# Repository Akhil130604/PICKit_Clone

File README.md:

# PICKit Clone #
📖 About The Project

This project aims to build a fully open-source, cost-effective clone of the Microchip PICKit programmer/debugger. While the original PICKit is a standard tool for PIC microcontrollers, this project seeks to provide a transparent hardware design and firmware implementation that can be studied, modified, and built by the community.

The goal is not just to replicate functionality, but to create a learning platform for embedded programmers and hardware designers interested in:

ICSP (In-Circuit Serial Programming) protocols.

USB Device implementations.

High-voltage generation circuits (VPP).

Low cost hardware.

## ⚠️ Current Status ##

Current Phase: 🚧 Hardware Design & Schematic Capture

We are currently in the initial design phase. The focus is on selecting components, finalizing the power architecture, and routing the initial PCB.

[ ] System Architecture Definition

[ ] Schematic Capture

[ ] PCB Layout

[ ] Prototype Assembly

[ ] Firmware Development

[ ] Testing & Validation

🛠️ Tech Stack & Tools

To view or edit the files, you will need:

EDA Tool: KiCad

Firmware IDE: MPLAB X IDE

## 📂 Repository Structure ##

The repository is currently messed up with unnecesssary files. you are welcome to rearrange it.

Note on Branches:

main: Contains stable, verified releases.

designing: The active design branch. All hardware work happens here.

firmware: The design and development of firmware happens here.

## 🚀 Getting Started ##

Clone the repository:

git clone [https://github.com/Akhil130604/PICKit_Clone.git](https://github.com/Akhil130604/PICKit_Clone.git)

Checkout the branch:

cd PICKit_Clone

git checkout branch

## 🤝 How to Contribute ##

We welcome contributions from the community! Whether it's a code fix, a better PCB routing suggestion, or documentation improvements.

Please read CONTRIBUTING.md for details on our code of conduct and the process for submitting pull requests.

## 📄 License ##

Distributed under the MIT License. See LICENSE for more information.

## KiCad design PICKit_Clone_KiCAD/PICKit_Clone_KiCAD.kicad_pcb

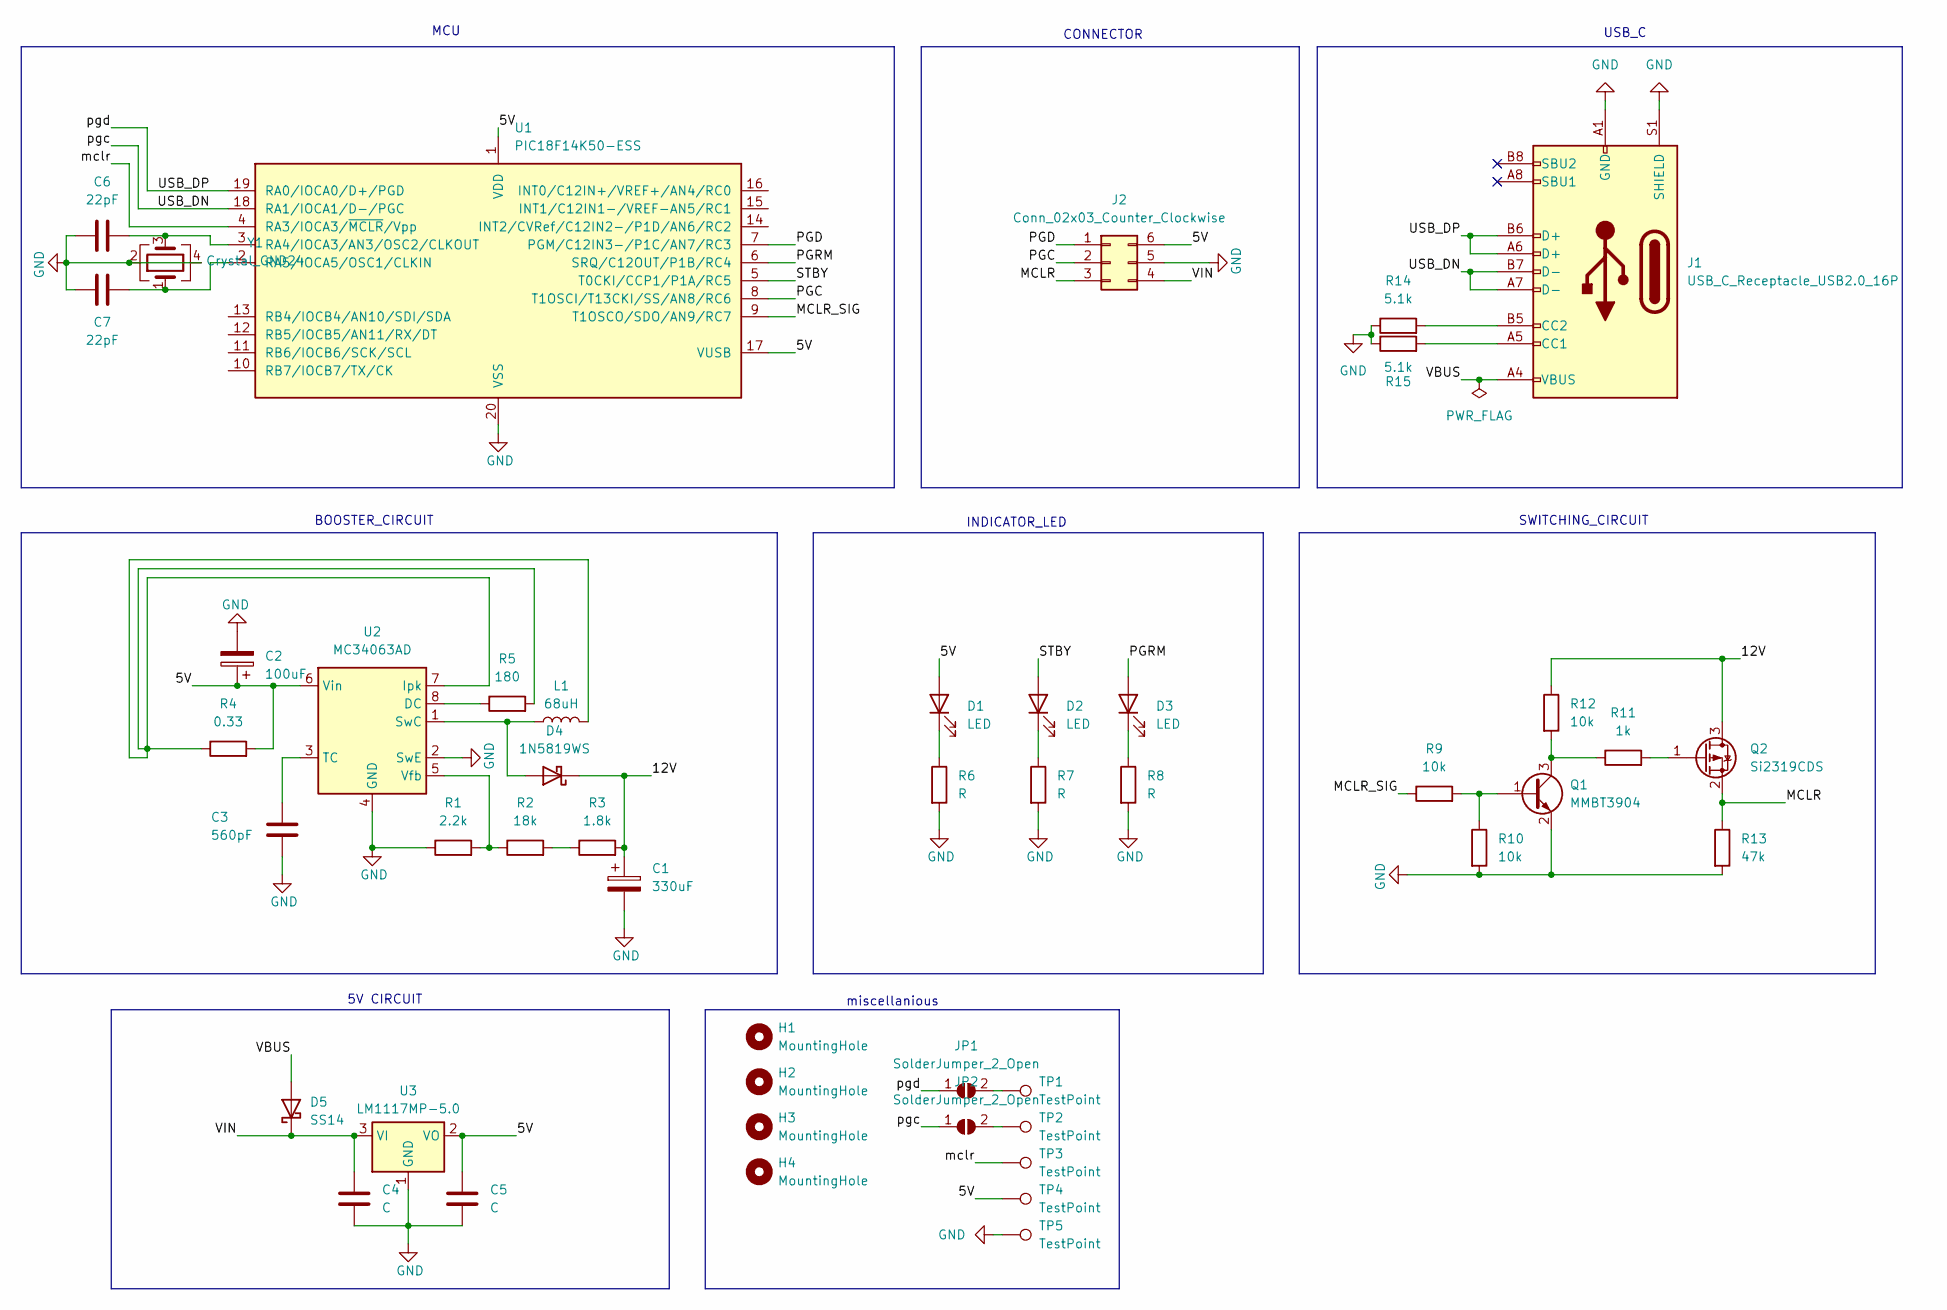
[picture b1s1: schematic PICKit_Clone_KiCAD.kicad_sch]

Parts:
C1: 330uF; CP_Elec_6.3x5.3
C2: 100uF; CP_Elec_6.3x5.3
C3: 560pF; C_1206_3216Metric_Pad1.33x1.80mm_HandSolder
C4, C5: C; C_1206_3216Metric_Pad1.33x1.80mm_HandSolder
C6, C7: 22pF; C_1206_3216Metric_Pad1.33x1.80mm_HandSolder
D1, D2, D3: LED; LED_1206_3216Metric_Pad1.42x1.75mm_HandSolder
D4: 1N5819WS; D_SOD-323_HandSoldering
D5: SS14; D_SMA
H1, H2, H3, H4: MountingHole; MountingHole_2.2mm_M2
J1: USB_C_Receptacle_USB2.0_16P; USB_C_Receptacle_G-Switch_GT-USB-7010ASV
J2: Conn_02x03_Counter_Clockwise; PinHeader_2x03_P2.54mm_Vertical
JP1, JP2: SolderJumper_2_Open; SolderJumper-2_P1.3mm_Open_Pad1.0x1.5mm
L1: 68uH; L_Sunlord_SWPA6045S
Q1: MMBT3904; SOT-23_Handsoldering
Q2: Si2319CDS; SOT-23_Handsoldering
R1: 2.2k; R_1206_3216Metric_Pad1.30x1.75mm_HandSolder
R2: 18k; R_1206_3216Metric_Pad1.30x1.75mm_HandSolder
R3: 1.8k; R_1206_3216Metric_Pad1.30x1.75mm_HandSolder
R4: 0.33; R_1206_3216Metric_Pad1.30x1.75mm_HandSolder
R5: 180; R_1206_3216Metric_Pad1.30x1.75mm_HandSolder
R6, R7, R8: R; R_1206_3216Metric_Pad1.30x1.75mm_HandSolder
R9, R10, R12: 10k; R_1206_3216Metric_Pad1.30x1.75mm_HandSolder
R11: 1k; R_1206_3216Metric_Pad1.30x1.75mm_HandSolder
R13: 47k; R_1206_3216Metric_Pad1.30x1.75mm_HandSolder
R14, R15: 5.1k; R_1206_3216Metric_Pad1.30x1.75mm_HandSolder
TP1, TP2, TP3, TP4, TP5: TestPoint; TestPoint_Pad_D1.0mm
U1: PIC18F14K50-ESS; SSOP-20_5.3x7.2mm_P0.65mm
U2: MC34063AD; SOIC-8_3.9x4.9mm_P1.27mm
U3: LM1117MP-5.0; SOT-223-3_TabPin2
Y1: Crystal_GND24; Crystal_SMD_3225-4Pin_3.2x2.5mm_HandSoldering

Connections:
/5V: C2.1, C5.1, D1.2 (A), J2.6, R4.2, TP4.1, U1.1 (VDD), U1.17 (VUSB), U2.6 (Vin), U3.2 (VO)
/12V: C1.1, D4.1 (K), Q2.3 (D), R3.2, R12.1
/MCLR: J2.3, Q2.2 (S), R13.1
/MCLR_SIG: R9.1, U1.9 (T1OSCO/SDO/AN9/RC7)
/PGC: J2.2, U1.8 (T1OSCI/T13CKI/SS/AN8/RC6)
/PGD: J2.1, U1.7 (PGM/C12IN3-/P1C/AN7/RC3)
/PGRM: D3.2 (A), U1.6 (SRQ/C12OUT/P1B/RC4)
/STBY: D2.2 (A), U1.5 (T0CKI/CCP1/P1A/RC5)
/USB_DN: J1.A7 (D-), J1.B7 (D-), JP2.1 (A), U1.18 (RA1/IOCA1/D-/PGC)
/USB_DP: J1.A6 (D+), J1.B6 (D+), JP1.1 (A), U1.19 (RA0/IOCA0/D+/PGD)
/VBUS: D5.2 (A), J1.A4 (VBUS), J1.A9 (VBUS), J1.B4 (VBUS), J1.B9 (VBUS)
/VIN: C4.1, D5.1 (K), J2.4, U3.3 (VI)
/mclr: TP3.1, U1.4 (RA3/IOCA3/~MCLR/Vpp)
GND: C1.2, C2.2, C3.2, C4.2, C5.2, C6.1, C7.1, J1.A1 (GND), J1.A12 (GND), J1.B1 (GND), J1.B12 (GND), J1.S1 (SHIELD), J2.5, Q1.2 (E), R1.1, R6.2, R7.2, R8.2, R10.2, R13.2, R14.1, R15.1, TP5.1, U1.20 (VSS), U2.2 (SwE), U2.4 (GND), U3.1 (GND), Y1.2, Y1.4
unnamed: D1.1 (K), R6.1
unnamed: D2.1 (K), R7.1
unnamed: D3.1 (K), R8.1
unnamed: D4.2 (A), L1.1, U2.1 (SwC)
unnamed: J1.A5 (CC1), R15.2
unnamed: J1.B5 (CC2), R14.2
unnamed: JP1.2 (B), TP1.1
unnamed: JP2.2 (B), TP2.1
unnamed: Q1.1 (B), R9.2, R10.1
unnamed: Q1.3 (C), R11.1, R12.2
unnamed: Q2.1 (G), R11.2
unnamed: R2.2, R3.1
unnamed: C6.2, U1.3 (RA4/IOCA3/AN3/OSC2/CLKOUT), Y1.3
unnamed: C7.2, U1.2 (RA5/IOCA5/OSC1/CLKIN), Y1.1
unnamed: R5.1, U2.8 (DC)
unnamed: L1.2, R4.1, R5.2, U2.7 (Ipk)
unnamed: C3.1, U2.3 (TC)
unnamed: R1.2, R2.1, U2.5 (Vfb)

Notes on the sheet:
USB_C
5V CIRCUIT
SWITCHING_CIRCUIT
INDICATOR_LED
BOOSTER_CIRCUIT
MCU
CONNECTOR
miscellanious

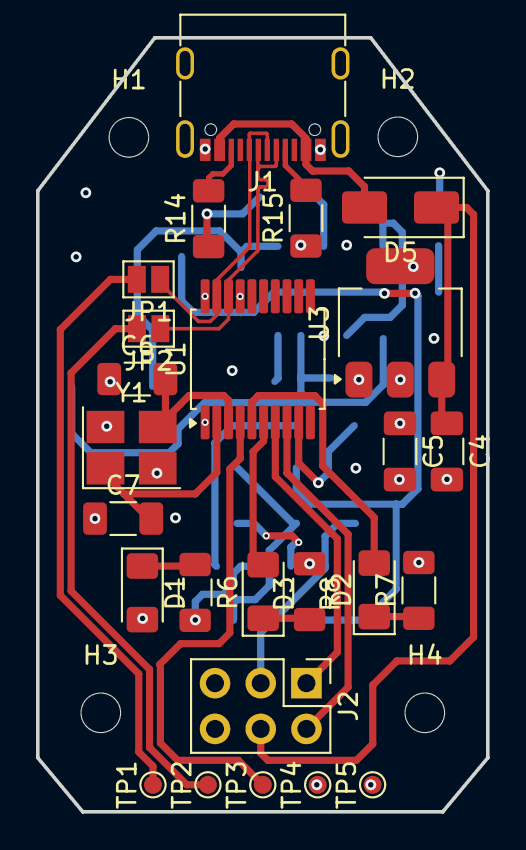
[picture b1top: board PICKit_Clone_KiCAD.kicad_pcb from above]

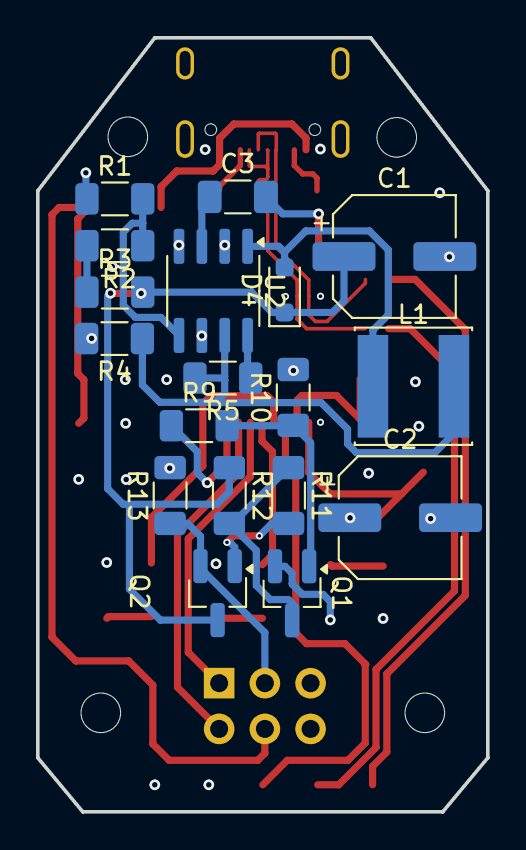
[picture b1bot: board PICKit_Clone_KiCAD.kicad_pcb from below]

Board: 4 copper layers, 25.0 x 43.0 mm, 47 parts (18 on the bottom side), 32 nets.

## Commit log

2025-09-09 Project initialization
    1)project has been initialized and basic configurations are done.
2026-01-13 PCB and CAD design
    1)PCB design of the board
    2)CAD design for the cover
2026-01-20 PCB and Design update
    1) PCB has been modified to include pads for initial programming of the MCU
    2)cover has been modified according to the new size of the PCB
2026-01-21 Add MIT License to the project
2026-01-21 Enhance README with project details and guidelines
    Added project overview, current status, tech stack, repository structure, and contribution guidelines to README.
2026-01-21 Add contributing guidelines for PICKit Clone project
    Added guidelines for contributing to the PICKit Clone project, including development workflow, hardware and firmware contribution rules, bug reporting, and code of conduct.
